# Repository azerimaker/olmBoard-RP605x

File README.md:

# olmBoard RP605K333B Buck-Boost Converter Module

Introducing our compact and ultra-low-power Buck-Boost Converter Module, designed using the high-performance RP605K333B DC/DC converter IC. This versatile module is perfect for powering a wide range of electronic devices, providing a stable 3.3V output (up to 300mA) from varying input sources ranging from 1.8V to 5.5V. This nifty little IC also features built-in Battery Monitor (BM) circuitry that, when enabled, divides the input voltage (VIN/3) and directly provides a buffered voltage to be measured by the ADC. These readings can be used to estimate the state of a battery.

Some specs: 

- Input voltage range (VIN): **1.8 V to 5.5 V**
- Output current: up to **300 mA**
- Output Voltage: **3.3V**
- Output Voltage Accuracy: **±1.5%**
- Operating quiescent current: **~300 nA**
- Shutdown current: **0.01 μA**
- Output DC/DC auto-discharge is included
- Efficiency: **~90%** in buck mode, **~75%** in boost mode
- Battery monitor: **VIN/3** typ. **0.1 μA** extra supply current
- Operating Temperature: **−40 to 85 °C**
- Module dimensions: **19.3 mm x 34.5 mm (0.76 in. x 1.36 in.)** with 4x M2 mounting holes

This DC/DC converter IC offers some unique features such as Variable Frequency Modulation (VFM) and built-in battery monitoring circuit with only 100 nA supply current. The module is breadboard friendly and all of the pins are broken out for easy interfacing. Additionally, there are two JST-PH connectors on input and output for easy battery and device connections.

### License:
- Hardware license: CERN-OHL-S v2
- Documentation license:  CC BY-SA 4.0 International.

### Contact:
If you have any question or comments please feel free to open an issue (or a discussion or drop me a message at [@makertronika](https://twitter.com/makertronika).

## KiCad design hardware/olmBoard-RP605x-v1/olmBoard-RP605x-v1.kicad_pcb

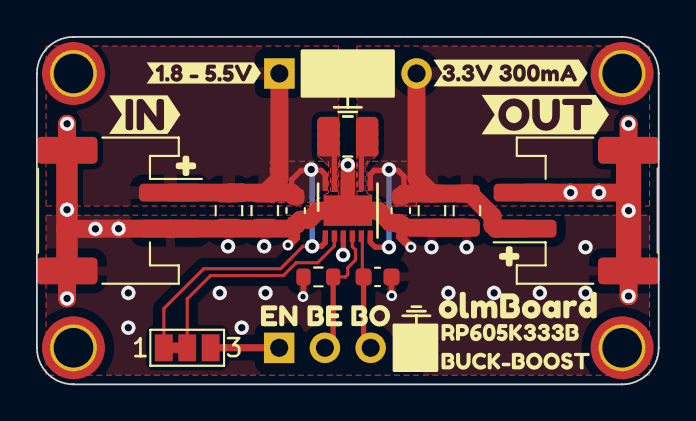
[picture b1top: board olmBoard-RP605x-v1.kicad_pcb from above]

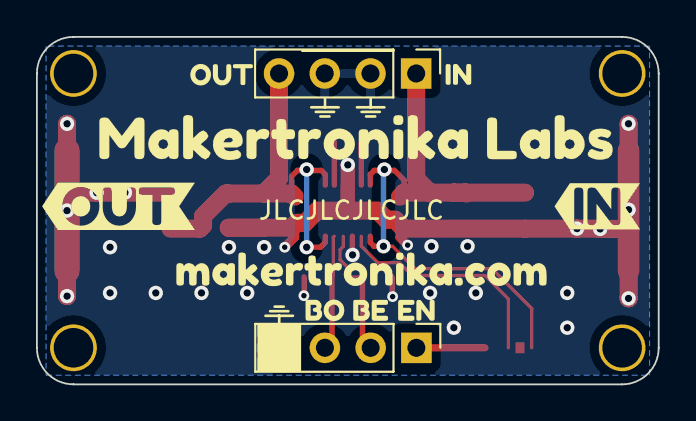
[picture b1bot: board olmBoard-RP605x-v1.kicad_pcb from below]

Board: 2 copper layers, 34.5 x 19.3 mm, 40 parts (11 on the bottom side), 9 nets.

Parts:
C1, C6, C7: 22uF; C_0805_2012Metric
C2, C3, C4: 100nF; C_0603_1608Metric
C5: 1uF; C_0805_2012Metric
G-logo: LOGO; makertronika-sm-8mm
H1, H2, H3, H4: MountingHole; MountingHole_2.2mm_M2_ISO7380_Pad_TopOnly
J1, J2: VIN; JST_PH_S2B-PH-SM4-TB_1x02-1MP_P2.00mm_Horizontal
J3: Conn_A; PinHeader_1x04_P2.54mm_Vertical
J4: Conn_B; PinHeader_1x04_P2.54mm_Vertical
JP1: EN; SolderJumper-3_P1.3mm_Bridged12_Pad1.0x1.5mm_NumberLabels
L1: 2.2uH; L_1008_2520Metric
R1: 100K; R_0603_1608Metric
U1: RP605K333B; DFN-12-1EP_2.7x3mm_P0.5mm_EP1.7x2.7mm
kibuzzard-658B4DF6: G***; kibuzzard-658B4DF6
kibuzzard-658B4DFC: G***; kibuzzard-658B4DFC
kibuzzard-658B4E8C: G***; kibuzzard-658B4E8C
kibuzzard-658B4E9D: G***; kibuzzard-658B4E9D
kibuzzard-65424F22, kibuzzard-65424F22#2: G***; kibuzzard-65424F22
kibuzzard-654250E5: G***; kibuzzard-654250E5
kibuzzard-654250EC: G***; kibuzzard-654250EC
kibuzzard-654258D9, kibuzzard-654258D9#2: G***; kibuzzard-654258D9
kibuzzard-654268F6: G***; kibuzzard-654268F6
kibuzzard-6542501C, kibuzzard-6542501C#2: G***; kibuzzard-6542501C
kibuzzard-6542684A: G***; kibuzzard-6542684A
kibuzzard-65425023, kibuzzard-65425023#2: G***; kibuzzard-65425023
kibuzzard-65426016: G***; kibuzzard-65426016
kibuzzard-65426020: G***; kibuzzard-65426020
kibuzzard-65426266: G***; kibuzzard-65426266
kibuzzard-65426283: G***; kibuzzard-65426283

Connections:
+3.3V: C4.2, C5.1, C6.2, J2.1, J3.4, U1.6 (VFB), U1.7 (VOUT)
BM_EN: J4.2, R1.2, U1.4 (CE2)
BM_OUT: C3.1, J4.3, U1.5 (BM)
EN: J4.1, JP1.3 (B)
GND: C1.1, C2.2, C3.2, C4.1, C5.2, C6.1, C7.1, J1.2, J1.MP (MountPin), J2.2, J2.MP (MountPin), J3.2, J3.3, J4.4, R1.1, U1.3 (AGND), U1.9 (PGND), U1.10 (PGND), U1.13 (PGND)
unnamed: JP1.2 (C), U1.2 (CE1)
unnamed: L1.1, U1.8 (BOLX)
unnamed: L1.2, U1.11 (BULX)
VCC: C1.2, C2.1, C7.2, J1.1, J3.1, JP1.1 (A), U1.1 (AVIN), U1.12 (PVIN)

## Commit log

2024-07-17 Initial hw files and readme added
